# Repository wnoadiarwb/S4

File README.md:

# S4
In-progress 4 Channel Solenoid Control via USB-MIDI

Based off the following circuit: https://www.instructables.com/Controlling-solenoids-with-arduino/

TODO: make user-friendly, make new board with raspberry pi pico, clean up screen print, component names, replace placeholder components with custom footprints, add BOM.

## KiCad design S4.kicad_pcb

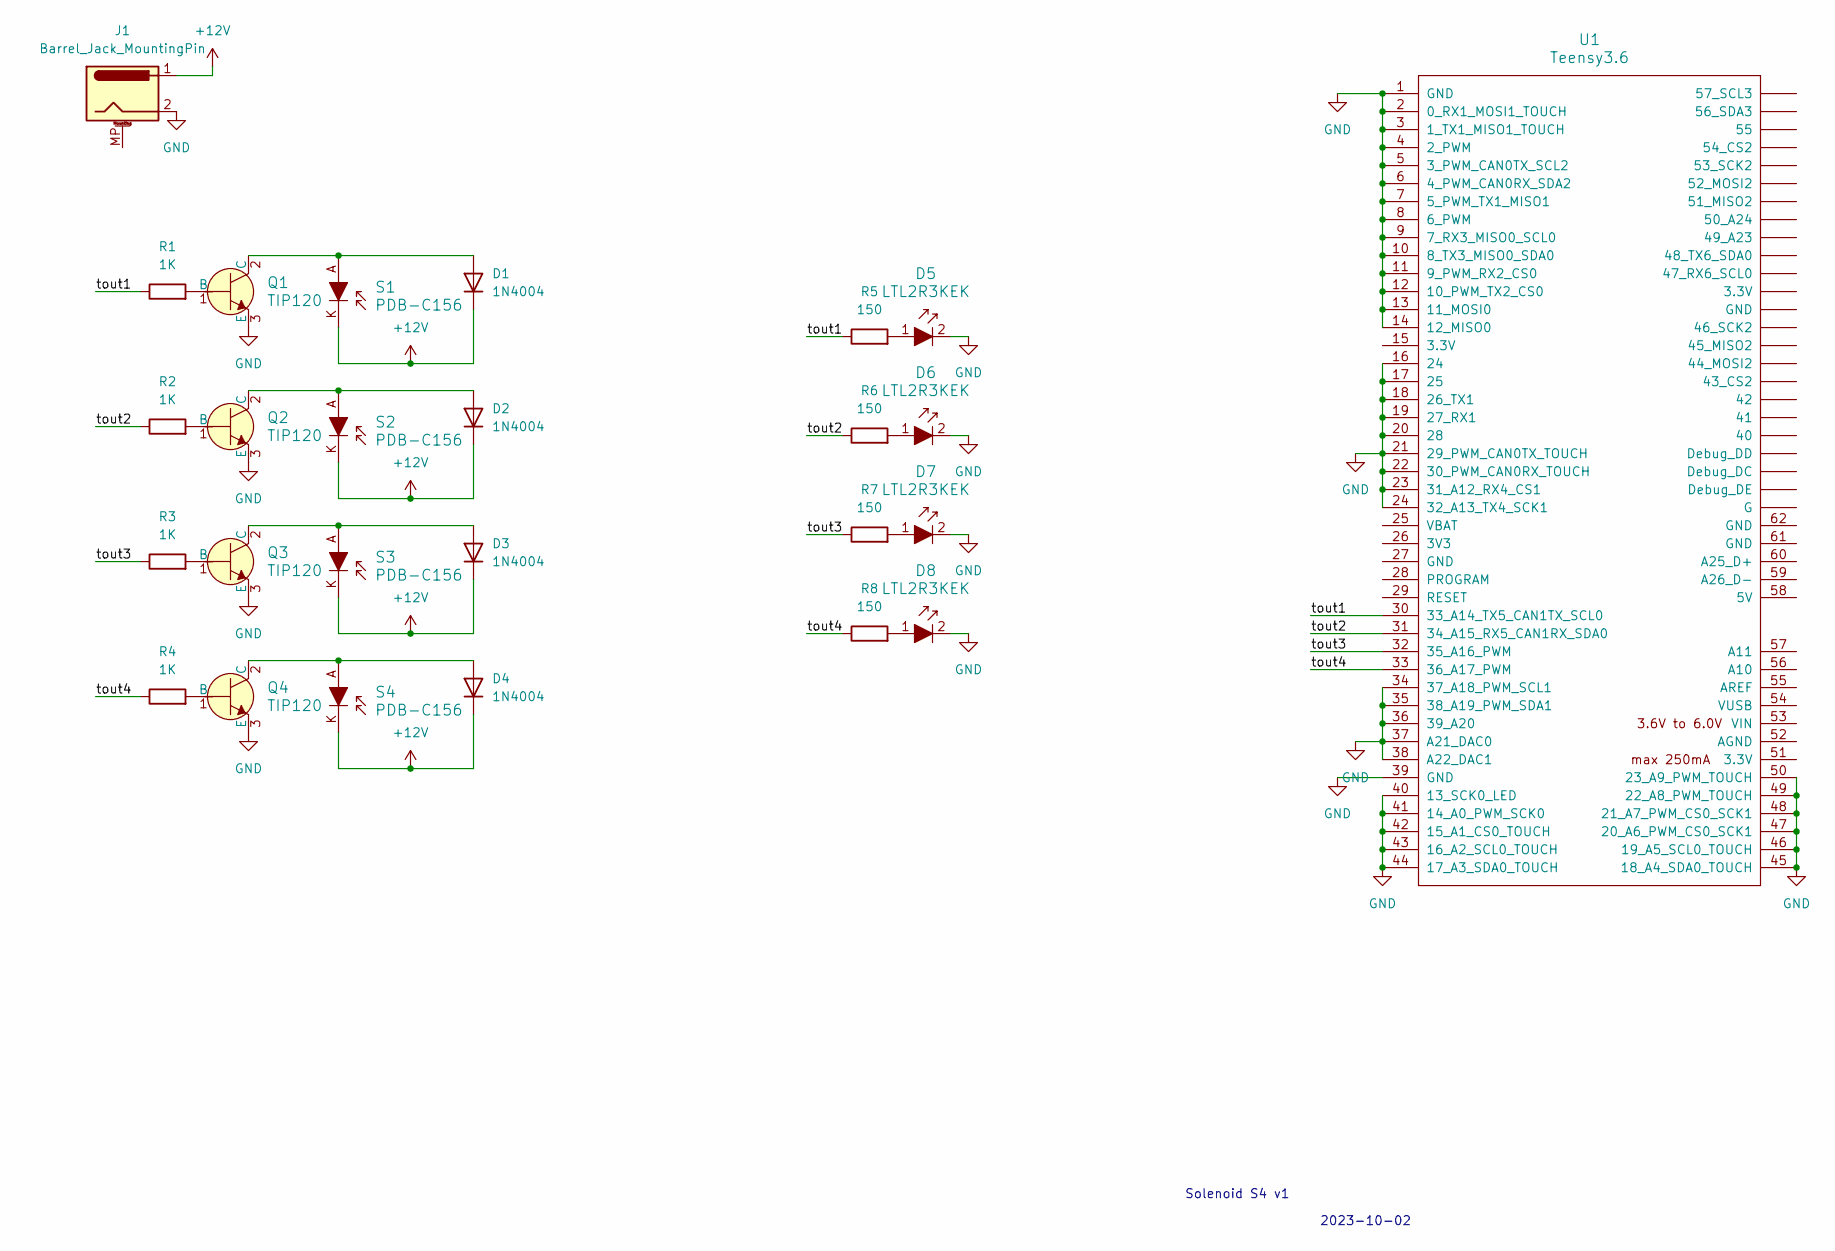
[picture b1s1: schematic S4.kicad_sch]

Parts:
D1, D2, D3, D4: 1N4004; D_DO-41_SOD81_P10.16mm_Horizontal
D5, D6, D7, D8: LTL2R3KEK; LED_5mm_Radial; MPN LTL2R3KEK; Digi-Key_PN 160-1682-ND
J1: Barrel_Jack_MountingPin; BarrelJack_Wuerth_6941xx301002
Q1, Q2, Q3, Q4: TIP120; TO-220-3; MPN TIP120; Digi-Key_PN 497-2539-5-ND
R1, R2, R3, R4: 1K; R_Axial_DIN0207_L6.3mm_D2.5mm_P7.62mm_Horizontal
R5, R6, R7, R8: 150; R_Axial_DIN0207_L6.3mm_D2.5mm_P7.62mm_Horizontal
S1, S2, S3, S4: PDB-C156; Photodiode_Radial_5.1x3mm_P2.54mm; MPN PDB-C156; Digi-Key_PN PDB-C156-ND
U1: Teensy3.6; Teensy35_36

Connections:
+12V: D1.1 (K), D2.1 (K), D3.1 (K), D4.1 (K), J1.1, S1.K, S2.K, S3.K, S4.K
/tout1: R1.1, R5.1, U1.30 (33_A14_TX5_CAN1TX_SCL0)
/tout2: R2.1, R6.1, U1.31 (34_A15_RX5_CAN1RX_SDA0)
/tout3: R3.1, R7.1, U1.32 (35_A16_PWM)
/tout4: R4.1, R8.1, U1.33 (36_A17_PWM)
GND: D5.2, D6.2, D7.2, D8.2, J1.2, Q1.3 (E), Q2.3 (E), Q3.3 (E), Q4.3 (E), U1.1 (GND), U1.2 (0_RX1_MOSI1_TOUCH), U1.3 (1_TX1_MISO1_TOUCH), U1.4 (2_PWM), U1.5 (3_PWM_CAN0TX_SCL2), U1.6 (4_PWM_CAN0RX_SDA2), U1.7 (5_PWM_TX1_MISO1), U1.8 (6_PWM), U1.9 (7_RX3_MISO0_SCL0), U1.10 (8_TX3_MISO0_SDA0), U1.11 (9_PWM_RX2_CS0), U1.12 (10_PWM_TX2_CS0), U1.13 (11_MOSI0), U1.14 (12_MISO0), U1.16 (24), U1.17 (25), U1.18 (26_TX1), U1.19 (27_RX1), U1.20 (28), U1.21 (29_PWM_CAN0TX_TOUCH), U1.22 (30_PWM_CAN0RX_TOUCH), U1.23 (31_A12_RX4_CS1), U1.24 (32_A13_TX4_SCK1), U1.34 (37_A18_PWM_SCL1), U1.35 (38_A19_PWM_SDA1), U1.36 (39_A20), U1.37 (A21_DAC0), U1.38 (A22_DAC1), U1.39 (GND), U1.40 (13_SCK0_LED), U1.41 (14_A0_PWM_SCK0), U1.42 (15_A1_CS0_TOUCH), U1.43 (16_A2_SCL0_TOUCH), U1.44 (17_A3_SDA0_TOUCH), U1.45 (18_A4_SDA0_TOUCH), U1.46 (19_A5_SCL0_TOUCH), U1.47 (20_A6_PWM_CS0_SCK1), U1.48 (21_A7_PWM_CS0_SCK1), U1.49 (22_A8_PWM_TOUCH), U1.50 (23_A9_PWM_TOUCH)
unnamed: D1.2 (A), Q1.2 (C), S1.A
unnamed: D2.2 (A), Q2.2 (C), S2.A
unnamed: D3.2 (A), Q3.2 (C), S3.A
unnamed: D4.2 (A), Q4.2 (C), S4.A
unnamed: D5.1, R5.2
unnamed: D6.1, R6.2
unnamed: D7.1, R7.2
unnamed: D8.1, R8.2
unnamed: Q1.1 (B), R1.2
unnamed: Q2.1 (B), R2.2
unnamed: Q3.1 (B), R3.2
unnamed: Q4.1 (B), R4.2

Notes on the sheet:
2023-10-02
Solenoid S4 v1

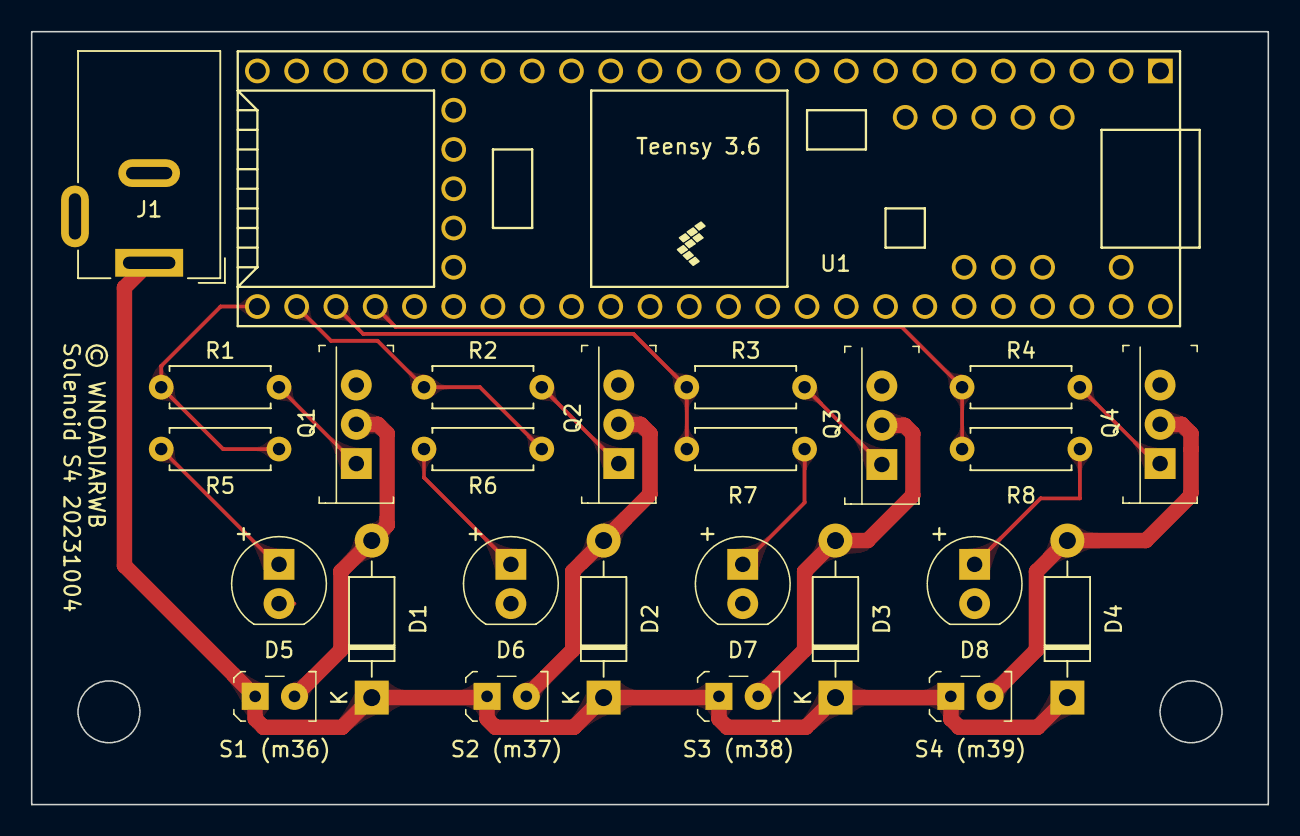
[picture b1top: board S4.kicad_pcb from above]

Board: 2 copper layers, 80.0 x 50.0 mm, 26 parts (0 on the bottom side), 18 nets.

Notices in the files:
S4.kicad_pcb:
© WNOADIARWB
